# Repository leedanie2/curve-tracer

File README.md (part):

# Curve Tracer

A low-cost semiconductor curve tracer for small-signal MOSFETs and diodes. It
sweeps the voltage across a device, measures the current through it with
four-wire (Kelvin) sensing, and streams the result over USB. A Python host then
fits the device's parameters (threshold voltage, transconductance, channel-length
modulation; diode ideality, saturation current and series resistance) and writes
them out as a SPICE `.model` card. The aim is to close the loop
`device → measurement → model → simulation` on hardware I designed.

It is built as an assembled PCB carrying an STM32 Nucleo-F303RE, with firmware
in C and a Python host.

## Status, 2026-11-13

Every claim below is one of five things. **Measured** means on the bench,
from the board. **Analysis** means arithmetic on measured figures, or a
comparison with published ones. **Simulated only** means LTspice, ngspice
or the firmware simulator, with no bench result yet. **Done** covers work that needs no
measurement. **Not done** is what's left. Nothing in this README goes past
its row.

| Claim | Status | Evidence |
|---|---|---|
| Analog design: stability into capacitive loads, current limiter, sense-amp CMRR | Simulated only | LTspice sims 02–11, [below](#simulation-results) |
| Schematic and 2-layer PCB, DRC/ERC clean, topology checker | Done | `hardware/review/pass2/` |
| Five boards fabricated and fully assembled by JLCPCB | Done | `hardware/ORDER.md` |
| Firmware runs on the Nucleo; host link works | Measured | 2026-10-30 to 2026-11-13 captures (`host/h4/`) |
| Board powers up; loop quiet into 200 Ω ‖ 100 nF (L1), idle and 0.1–6 V | Measured | 2026-11-03 and 2026-11-08, [bench record](#bench-record) |
| 100 nF alone across a two-terminal device keeps the loop quiet, on a breadboard fixture | Measured, 2026-11-13: idle, 0.2–6 V, beside 0.1% resistors and through a diode sweep. Sim 16 predicted it. MOSFET families stay on L1 | [Session 3](#session-3-board-2-2026-11-13) |
| Loop stable with nothing connected (C1 empty) | **Measured: fails.** Oscillates at 0.8–1.15 MHz | [The open-load oscillation](#a-measured-finding-the-open-load-oscillation) |
| Root cause of the oscillation | Analysis and simulation | Sims 12–14 |
| C1 in the 2.2–4.7 pF range damps it | Simulated only (TI's op-amp model, open load and 200 Ω ‖ 100 nF) | Sims 14–14f; not fitted, since 0603 can't be hand-fitted here. Rev 2 specifies 4.7 pF |
| 470 Ω across the device keeps the loop quiet | **Measured: fails.** Oscillates at 781 kHz with nothing running. Sim 13 had predicted quiet | [Working around it](#working-around-it-until-rev-2) |
| L1 (200 Ω ‖ 100 nF) across the device keeps it quiet, and why | Measured; the mechanism is analysis and simulation (sim 15) | [Working around it](#working-around-it-until-rev-2) |
| Voltage accuracy against a DMM | Measured, 3 points: within the DMM's own ±0.8%. Blueprint §7's < 0.5% needs a better reference | [Accuracy](#accuracy-against-a-dmm) |
| Current against voltage, 0.1% resistors | **Measured**, 2026-11-13: current reads 0.1–0.8% high against the voltage, or up to 1.5% if the resistors sat behind the fixture's ~0.5 Ω (analysis; MVP card §F decides). Zero −0.09 to −0.14 mA. Absolute current ±1.6% (±2.3%) uncorrected, set by the voltage's DMM check | [Session 3](#session-3-board-2-2026-11-13) |
| The current channel with nothing drawing current | **Measured**: it reads a floor, 0.198 + 0.104 · V mA, not its zero; the difference amp's swing limit (analysis, TI's datasheet). The host leaves such rows out | [Session 3](#session-3-board-2-2026-11-13) |
| R_p subtraction, channel model, extraction, `.model` card, ngspice overlay | Done; run on bench data 2026-11-08 and 2026-11-13 | `host/`, 203 tests |
| Diode parameters from a real diode | **Measured**: 1N4148, n 1.789, I_S 2.68 nA, R_s 1.14 Ω. Systematic from the zero and the channel model: n 1.788–1.831, I_S 2.15–3.69 nA, R_s 1.01–1.14 Ω | [Headline figure](#headline-one-real-diode-measured-and-simulated) |
| Measured vs simulated overlay, real diode | **Measured**, against ngspice running the extracted card: 0.51 mV rms over 0.2–20 mA | [Headline figure](#headline-one-real-diode-measured-and-simulated) |
| Diode against published 1N4148 models | Analysis: between LTspice's and Nexperia's, 8–24 mV from each | [Session 2](#session-2-board-2-2026-11-08) |
| MOSFET `.model` card from a real part | **Fixture-dependent, under investigation.** Measured 2026-11-13 (2N7000, Level 1, 16 gate steps, saturation only), but on a fixture that put ~0.4 Ω in its source path (analysis), and 86 mV of gate from the same part on 11-08 is unexplained. Not a headline result | [The 2N7000 card](#the-2n7000-card-fixture-dependent-under-investigation) |
| MOSFET threshold | **Measured**, 2026-11-08: **V_GS(th) 2.147 V at 1 mA**, model-free; the measured threshold. The same part on 11-13 needed ~90 mV more gate, under investigation | [Session 2](#session-2-board-2-2026-11-08) |
| Waves on the scope with a MOSFET in place | Measured on the scope: 748 kHz in an 11-08 hold; none in an 11-13 hold; waves during both sweeps. Under 10 µA in the DC readings. Sustained or not: open | [Session 3](#session-3-board-2-2026-11-13) |
| Blueprint §6 closed loop: build a circuit with the extracted model, compare | Not done | |
| Short-circuit and thermal test (H4 Block 4) | Not done | No heatsink insulator at the bench |
| Current ranges 2 and 3 (fitted on the board) | Not done | Out of scope |

### Headline: one real diode, measured and simulated

*Measured, 2026-11-08, board 2: a 1N4148 swept to 20 mA, four-wire,
`device → measurement → model → simulation` closed on real data. The dots
are the measurement, with L1's current and the instrument's zero subtracted
(`host/h4/mvp_17_diode_rp.csv`). The line is ngspice-47 running the
`.model` card the host fitted from those dots
(`host/h4/mvp_17_diode.lib`: n 1.789 ± 0.003, I_S 2.68 ± 0.06 nA,
R_s 1.135 ± 0.016 Ω, statistical). **The larger uncertainty is
systematic.** The instrument's current zero measured −0.087 mA on the
calibration and −0.099 mA on the diode's own off rows. Refitted at each,
the values span n 1.788–1.831, I_S 2.66–3.69 nA, R_s 1.01–1.14 Ω. The
0.1% resistor holds of 2026-11-13 add two smaller terms. Current reads
0.1–0.8% high against voltage, and the voltage channel may read 10 mV low.
That would take I_S to 2.15 nA, so in all **n 1.788–1.831, I_S
2.15–3.69 nA, R_s 1.01–1.14 Ω**. n and I_S trade off against each other,
so the curve itself moves at most 3 mV, or 10 mV with the voltage
offset. Residual 0.51 mV rms over the 60 points above 0.2 mA. Of that, −0.38 mV is a constant: ngspice's default 27 °C against
the fit's 300 K. Hollow points sit below 5 current LSB and are not fitted.
The curve lies between the two published 1N4148 models compared, 8–24 mV
above LTspice's and 10–14 mV below Nexperia's (diode temperature not
measured; ~2 mV/°C).*

*Why this capture stays the headline after a second one (2026-11-13).*
On 11-08 L1 lifted every reading clear of the current channel's floor, and
its own calibration line gave the zero at the same voltages. The 11-13
capture, on 100 nF alone, has 39 of 100 rows on the floor, so its zero has
to be borrowed from holds at other voltages. Its n also moves 2.5× more
with the low-current cut. That rule was set before comparing values
([session 3](#session-3-board-2-2026-11-13)). The 11-13 diode reads 23–44 mV
higher at equal current, and it is the same diode. A fixture resistance
of ~0.5 Ω between the Kelvin points and the part accounts for its higher
R_s, and for 0.6 mV of the 22 mV at 1 mA. The rest is unexplained
(analysis; MVP card §F tests it).

*KiCad render of the routed board (Pass 2, 2026-10-06), not a photograph. The
Nucleo plugs into the two sockets on the right. Board size 135 × 92 mm, two
layers.*

## What it can measure

The design envelope. Nothing in it is measured yet unless the row says so.

| | |
|---|---|
| **Devices** | Two-terminal devices (diodes, LEDs, resistors) and **N-channel enhancement MOSFETs**. **No BJTs**: the step source is a voltage through 1 kΩ, not a base current. **No P-channel or depletion parts**: the gate source is 0 to +10 V |
| **Polarity** | **One quadrant.** Drain/anode at 0 to +10 V and current into the device only. No reverse bias |
| **Voltage** | 0–10 V by design; 9.06–9.73 V is the ceiling at 50 mA (analysis: the PTC fuse's drop). **Floor measured: 0.18 V** at the node (DAC code 0, 2026-11-08), well below the 0.66 V the DAC's guaranteed 0.2 V minimum implies. Above ~6.6 V the Nucleo's LED loads the DAC: estimated, not measured |
| **Current** | 0–50 mA on range 1, 40.3 µA per ADC count, averaged 64× per point. Hardware limiter ~75 mA (simulated); firmware limit set per device. **Floor measured:** with nothing lifting it, the channel reads no lower than 0.198 + 0.104 · V mA, so on 100 nF alone a device registers only above ~0.4–0.5 mA at 0.6 V; on L1, from 0.2 mA |
| **Mode** | **DC only.** No pulsed mode, so the device heats at its own dissipation |
| **Accuracy** | Voltage: within a 3½-digit DMM's ±0.8% (2026-11-08). Current against voltage: 0.1–0.8% high, from 0.1% resistors (2026-11-13), or up to 1.5% if they sat behind the fixture's ~0.5 Ω. So absolute current is ±1.6% (±2.3%) uncorrected. Zero −0.09 to −0.14 mA, subtracted. [DMM](#accuracy-against-a-dmm), [resistors](#session-3-board-2-2026-11-13) |
| **Until rev 2** | The loop needs ≥ 100 nF across the device. **Two-terminal parts:** 100 nF alone, on a breadboard fixture (measured quiet, 2026-11-13), with nothing to subtract. **MOSFET families, and a diode's bottom decade:** L1, 200 Ω ‖ 100 nF. The host subtracts L1's current from a calibration sweep (~1.5 µA at 0.75 V on 2026-11-08), and L1 lifts the channel off its floor. A plain 470 Ω was not enough (measured) |

**What it's for.** It replaces the undergraduate I-V lab done by hand with
a bench supply and two meters, one point at a time, for small diodes, LEDs
and small N-MOSFETs. It records the curve with four-wire sensing and fits a
SPICE model from it. **What it isn't:** a general-purpose commercial curve
tracer or source-measure unit. Those cover high voltage and current, both
polarities, pulsed measurement, BJTs and picoamp leakage. This covers none of
them.

## Limitations

What the results above do not cover, as of 2026-11-13:

- **Waves on the scope with a MOSFET in place are unexplained.** On 11-08
  a hold's counter locked at 748.5 kHz; on 11-13 a hold showed nothing
  periodic, but waves showed during both family sweeps. They move the DC
  readings by under 10 µA. Whether they are sustained, and which loop they
  come from, is open.
- **The gate voltage is commanded, not read back.** The read-back step
  (H4 P1b) was skipped, so every V_GS, including the 2N7000's threshold,
  carries the gate DAC's unmeasured gain error.
- **The MOSFET card is narrow and fixture-dependent.** It is Level 1,
  fitted over V_GS 2.45–2.75 V, and holds in saturation only: below
  V_DS ≈ 0.4 V it reads up to 4.2 mA low, because the part is in moderate
  inversion. It was taken on a fixture that degenerated the source by
  ~0.4 Ω (analysis). It stays under investigation until MVP card §F reruns
  it with the Kelvin pair and the force wires at the part.
- **The same two parts read differently from one session to the next.** On
  11-13 the 1N4148 read 23–44 mV higher, and the 2N7000 needed ~90 mV more
  gate, than on 11-08. *Analysis:* ~0.4–0.6 Ω of breadboard links
  between the Kelvin points and the parts explains the resistive part of
  both, and of L1's fitted R. It can't explain a constant +21 mV on the
  diode or +86 mV of gate. Self-heating during the sweeps can't either: it
  is under 0.3 K per sweep, and the 2N7000's is the wrong sign. That leaves
  the parts' surroundings, which weren't measured. The constants are
  unexplained.
- **Blueprint §6's closed loop is not done.** The diode's model is checked
  against its own measurement. No circuit has been built around it and
  compared with the bench.
- **Absolute accuracy rests on a 3½-digit DMM.** The 0.1% resistors fix
  current against voltage to 0.1–0.8% (1.5% if the fixture's resistance
  sat in series with them), but voltage itself is bounded only at the DMM's
  ±0.8%. Part of the spread is one open question: a −10 mV voltage offset,
  or a curved common-mode term. Section F's holds decide both.
- **The bench supply can be off without the instrument knowing.** Nothing
  reads +15 V. On 11-13 three runs were taken with it off and produced
  plausible numbers; the card now checks the supply's display after every
  part swap.

## A measured finding: the open-load oscillation

**Measured, 2026-11-03, board 2, C1 empty.** Holding 6 V into
200 Ω ‖ 100 nF, the loop was quiet. With nothing connected it oscillated
intermittently at **0.79–1.15 MHz**, from over 0.2 V to over 2 V
peak-to-peak (the scope clipped). In the run with the largest
oscillation, the current read 2.2 mA high. (The other two runs' 0.83 mA,
first read as error too, is the channel's floor with nothing drawing
current, measured on 2026-11-13 with the loop quiet.) Full data is in
[Block 1](#block-1-measurements-first-power-up-board-2) below and in
[`docs/characterization.md`](docs/characterization.md).

**Root cause (analysis, checked in LTspice sims 12–14).** With no load, the
pass transistor (Q1) carries only ~0.2 mA. Its emitter resistance is then
~130 Ω, and it drives the ~1 nF of the protection diode D3 through ~41 Ω.
That puts a pole near 0.8 MHz inside the loop. Under the 200 Ω load, Q1 runs
at 26 mA and the pole moves far out. So the problem depends on the load,
which is why it shows up well below the ~3 MHz the design had estimated for
the op-amp's input-capacitance pole. The generic op-amp model reproduces
the oscillation only with 20–30 pF of input capacitance added. TI's own
OPA2197 model needs none: at open load it rings at 0.91 MHz, each
half-cycle 0.83× the last, close to sustained.

**The fix (simulation, sims 14–14f, TI's model).** The board has an empty
footprint for C1, a capacitor across the feedback resistor. The predicted
value is **3.4–3.9 pF**. At 6 V open load, 3.3 pF cuts the ring to 0.40×
per half-cycle, and 4.7 pF removes it, with no sign of over-compensation.
The generic model's figure, 8.6–12.9 pF, would over-compensate. Because the
bench was less damped than TI's model, rev 2 specifies **4.7 pF**
(`hardware/DECISIONS.md` R2-4). That rests on one vendor model. C1 is a
0603 part, which I can't fit reliably by hand, so it isn't fitted on rev 1.
Rev 2 has the assembler fit it.

### Working around it until rev 2

**Measured, 2026-11-08.** Sim 13 predicted that 470 Ω clamped across the
device would keep the bare loop quiet. On the bench it didn't: with nothing
running, 470 Ω oscillated at **781 kHz**, over 205 mV peak-to-peak. The
loop is never fully off. The sweep DAC can't reach 0 V, so at idle it holds
the node at 0.18 V, and that is where 470 Ω failed. L1, the
200 Ω ‖ 100 nF load from Block 1, was quiet at idle and at every level
tried, 0.1–6 V. So every device now shares J6 with L1, and the host
subtracts L1's current, calibrated by a sweep of L1 alone.

**Why it is the 100 nF (analysis, checked in sim 15 with TI's model).**
The load puts a lag of 20–30° into the loop. Without the 100 nF that lag
sits at 1.5–5 MHz, around crossover, on top of the op-amp's own excess
phase. With it, the same lag moves two decades down, to 20–60 kHz, where
the loop has phase to spare. L1 also biases Q1 harder (0.9 against
0.4 mA). In sim 15 that only shrinks a ring the 100 nF removes outright.
Sim 13's error was its model. The generic op-amp with 20–30 pF added had
been fitted to reproduce one bench point, the open-load oscillation, and
it was optimistic everywhere else. TI's model is optimistic too, though
less so: it rings and decays where the bench sustained. Phase 0 had the
same lesson about the BD139 model (design decision 2 below).

**100 nF alone, on a breadboard fixture (measured, 2026-11-13).** Sim 16
said the capacitor, not the resistor, was doing the work, and the bench
agreed. With only 100 nF across D–S, plugged into a breadboard with the
Kelvin pair at the device's own columns, the loop showed no periodic wave
at idle, at 0.2, 1 and 6 V, beside 0.1% resistors, or through a diode
sweep. Two-terminal parts no longer need L1, so there is no current to
subtract. MOSFET families still do: with no resistor, the node can't
discharge between gate steps below ~0.6 V. One practical lesson: the
breadboard's centre channel splits each column. The first MOSFET attempt
had its legs across it, its gate was undriven, and the family came out
flat.

## Design decisions

Each of these is backed by a simulation, a calculation or a datasheet figure.
The full record, part by part, is [`hardware/DECISIONS.md`](hardware/DECISIONS.md);
the reasoning is in [`curve_tracer_blueprint.md`](curve_tracer_blueprint.md).

1. **Isolate the capacitive load; don't compensate it.** The obvious fix, a
   capacitor across the feedback resistor, made the loop *worse* at every value
   from 1 to 100 pF. Instead, a 22 Ω `R_iso` sits outside the loop, and Kelvin
   sensing makes its 1.1 V drop at 50 mA harmless (sims 02, 03).
2. **Model fidelity decided the answer.** With a generic 2N2222 model the
   loop looked unconditionally stable. ST's published BD139 model (f_T ≈ 54 MHz,
   C_jc 36 pF) oscillated immediately. A third-party BD139 model found online
   had placeholder junction capacitances (`CJE = CJC = 1e-11`) and would have
   hidden the problem. A separate false result, 9% overshoot, turned out to be
   a solver timestep artefact. Capping the timestep removed it
   (blueprint §12).
3. **Base resistor 330 Ω, not 680 Ω.** Both are stable in simulation, but
   680 Ω leaves ~44° of implied phase margin, against ~59° for 330 Ω. The
   op-amp's own input capacitance adds a pole the simulation does not contain
   (estimated 5–9 pF), and from 44° that loss is not recoverable (sim 08).
4. **A base-emitter clamp diode.** On a falling edge the op-amp slams to its
   rail while the load holds the emitter up, and V_BE reaches −9 V against the
   BD139's 5 V rating. A 1N4148 holds it to −0.74 V (sims 08, 09).
5. **A hardware current limiter**, Q2 across a 10 Ω `R_sense`, independent of
   the firmware limit. 15 Ω was rejected because its trip point (~49–50 mA)
   falls inside the sweep range (sims 10, 11).
6. **Buffer the difference amplifier's inputs.** Unbuffered, the resistor
   bridge alone draws 475.6 µA through the shunt with nothing connected. That
   is 0.95% of full scale on range 1 and makes range 3 unusable. The design
   went from two to three dual op-amps (sims 06, 07).
7. **0.1% resistors in the difference amp**, because common-mode rejection
   comes from resistor matching alone and cannot be trimmed afterwards (sims 04,
   05).
8. **One board revision, designed for it.** There is a test point on every
   node, footprints for alternate values, headers instead of soldered
   connections, and a footprint for the compensation capacitor, left empty.
   JLCPCB assembled every part on all five boards.
9. **The host slices on *measured* voltage, never the commanded voltage.** At
   one commanded voltage, curves at different currents reach different real
   voltages because of `R_iso`'s drop. Grouping by the command gives a
   convincing but wrong threshold voltage. The diode fit solves n, I_S and R_s
   jointly; a windowed semilog fit was 13% wrong on n at R² = 0.9965
   ([`host/README.md`](host/README.md)).

Two decisions changed when they met reality. They are recorded as rev-2 items,
not hidden:

- **The F303RE has no DAC2.** The board routed the sweep to a pin with no DAC.
  This was found at the first real firmware build. The fix is a jumper on the
  Nucleo from PA5 (DAC1_OUT2) to PA6. PA5 also drives the Nucleo's LED, which
  loads the DAC and may cut sweeps above about 6.6 V (estimated, not yet
  measured; `DECISIONS.md` R2-3).
- **The empty compensation-capacitor footprint assumed hand-fitting**, a
  0603 part, which I could not do reliably. Rev 2 has JLCPCB fit it, at
  4.7 pF (`DECISIONS.md` R2-2, R2-4).

## Simulation results

**All of these are simulated.** LTspice files are in [`sim/`](sim/), with
per-file detail in [`sim/README.md`](sim/README.md). The sweep-source sims
ran at R_f = 23.3 kΩ; the board has 23.2 kΩ, a 0.4% difference below the
precision of every figure here.

| Question | Result (simulated) | Simulation |
|---|---|---|
| Capacitive load the sweep source tolerates | Without `R_iso`: stable to ~1 nF, oscillating by 2.2 nF. With 22 Ω: clean from 100 pF to 100 nF | LTspice, `sim/03_sweep_source_load_sweep.asc` |
| Small-signal step, 100 nF ‖ 200 Ω, R_B = 330 Ω | 10.34% overshoot, 0.50 µs to 1%, ζ ≈ 0.59 (~59° implied phase margin) | LTspice, `sim/08_sweep_source_rb_sweep.asc` |
| Reverse V_BE on a falling edge, 100 nF load | −7.72 V → −0.73 V (200 Ω load); −8.98 V → −0.74 V (open), with the clamp | LTspice, `sim/08…`, `sim/09_sweep_source_clamped.asc` |
| Current-limiter trip; hard short | 75.2 mA through R_sense; 107.0 mA load; BD139 at 891 mW | LTspice, `sim/11_limit_sizing.asc` |
| Overshoot on recovery from a short, 100 pF load | 14.8 V peak (+48%); back within 1% in 1.9 µs | LTspice, `sim/10_current_limit.asc` |
| Difference-amp CMRR, worst-case 0.1% corner | 74.42 dB | LTspice, `sim/04_diffamp_cmrr.cir` |
| CMRR, 500-run Monte Carlo at 0.1% | median 88.26 dB, p5 79.43 dB, min 76.20 dB | LTspice, `sim/05_diffamp_mc.cir` |
| Phantom current, unbuffered diff amp, no DUT | 475.6 µA at 1 Ω shunt | LTspice, `sim/06_diffamp_loading.cir` |

*Simulated: CMRR over 500 Monte Carlo runs with 0.1% resistors
(`sim/05_diffamp_mc.cir`). LTspice draws uniform, independent tolerances, so
this spread is conservative.*

Sims 02–11 didn't model D3's ~1 nF, the PTC or the Kelvin divider; sim 12
added them. That is the gap the board fell into at open load: see
[the finding](#a-measured-finding-the-open-load-oscillation).

### Host software, closed loop on a simulated device

`ct_sim` is the real firmware core (sweep engine, CSV writer, command parser,
current limit), compiled for the desktop with a modelled device behind it. The
host's tests feed it known parameters, run a sweep, extract the parameters, and
require the same values back. **Simulated, `ct_sim`:**

| Fed in | Recovered |
|---|---|
| V_th = 2.15 V | 2.1502 V (0.2 mV) |
| k = 0.055 A/V² | 0.05506 (0.1%) |
| λ = 0.012 /V | 0.01192 (0.7%) |
| diode n = 1.75 | 1.7605 (0.6%) |
| diode I_S = 2.5 nA | 2.73 nA (9%; quantisation, explained in [`host/README.md`](host/README.md)) |
| diode R_s = 0.6 Ω | 0.5914 Ω (1.4%) |

With a 470 Ω resistor beside the device, its current subtracted, and the
extracted card run back through ngspice, the simulated diode comes back as
n = 1.751, I_S = 2.52 nA and R_s = 0.601 Ω, with a 0.63 mV rms residual
([`host/README.md`](host/README.md#from-a-capture-to-the-overlay)). 203
host tests and the firmware unit suites pass. That validates the software
path only. It says nothing about the analog hardware.

## Block diagram

```
   Nucleo-F303RE                     Board
  ┌──────────────┐
  │ DAC1_OUT2 PA5├─shunt─► PA6 ─► [×3.32] ─► [OPA2197 + BD139 follower] ─► R_sense ─┬─► R_iso 22Ω ─► PTC ─► shunt ─► DUT drain
  │              │                                ▲      │                         │                        │            │
  │              │                                │   [Q2 current limiter]        │                   [buffered     [Kelvin pair
  │              │                                └─────────── feedback ──────────┘                   diff amp ×20]  ÷4 + buffer]
  │ ADC1  PA0   ◄├──────────────────────────────────────────────────────────────────────────────────────────┘            │
  │ ADC2  PC0   ◄├───────────────────────────────────────────────────────────────────────────────────────────────────────┘
  │ DAC1_OUT1 PA4├─────► [×3.32] ─► [buffer] ─► 1 kΩ ─► DUT gate  (12 V Zener clamp)
  │ USART2 ◄─────┼─► ST-LINK VCP ─► USB ─► Python host
  └──────────────┘                                                     DUT source ─► GND        (SMAJ12A TVS on the drain)
```

Per point: set the gate DAC, set the drain DAC, wait to settle, oversample both
ADCs 64×, send a CSV row. The host recomputes current and voltage from the raw
accumulators and checks them against the firmware's own numbers.

## PCB

*KiCad render, top view (`hardware/review/pass2/`). The analog section is on the
left, with the Nucleo sockets J7/J8 on the right. Q1's heatsink keep-out is
marked at the top left.*

- The analog-critical nets were routed by hand: the feedback node, the
  inverting input, the base drive, the shunt and Kelvin pairs. The rest was
  autorouted (Freerouting) with those nets locked
  ([`hardware/README.md`](hardware/README.md), *Routing policy*).
- DRC and ERC are clean with schematic parity
  (`hardware/review/pass2/metrics.txt`). `check_topology.py` asserts the
  circuit's topology from the netlist (59 checks) and catches all 14 faults
  its self-test plants, which ERC passes.
- Every net that crosses the ground split, and its distance to the star
  tie: [`p2_split_crossings.png`](hardware/review/pass2/p2_split_crossings.png).

## A bench finding: the ST-LINK serial link on macOS

The first time the host talked to the Nucleo (2026-10-30), every command timed
out. A single host write of **16 bytes or more** stopped the ST-LINK/V2-1's
virtual COM port passing data from host to target until the USB cable was
replugged. This was on firmware V2J33M25, under macOS. Writes of 8 bytes,
5 ms apart, got through. The first write after the ST-LINK enumerates was also
lost.

To rule out the firmware, I read the MCU state over SWD while the link was
wedged. The main loop was idle, USART2 was configured, and no bytes were
reaching the RX pin (PA3). The fault is upstream of the MCU, in the ST-LINK's
USB-to-UART bridge. The fix is host-side: the transport writes in 8-byte
chunks 5 ms apart and opens with a blank line, which the firmware's parser
ignores. A regression test checks that no single write reaches 16 bytes. After
the fix, two hold runs back to back worked after a replug (commit `2debc57`).
An ST-LINK firmware upgrade might also fix it. That is untested.

## Bench record

### Block 1 measurements: first power-up, board 2

**Measured, 2026-11-03**, from [`hardware/MVP_CARD.md`](hardware/MVP_CARD.md)
(raw data in `host/h4/mvp_*.csv`; full log in
[`docs/characterization.md`](docs/characterization.md)). A pass here shows
no sustained oscillation under a DC hold. It does not measure phase margin
or ringing (H4 step 5, not run). C1, the compensation capacitor, is empty.

| Measurement | Pass band | Result |
|---|---|---|
| Supply current at power-up | 3–25 mA | 3 mA, supply in CV (rails not checked) |
| Scope baseline at TP3, idle (B) | < 10 mV p-p | 12.0 mV, board powered |
| Hold 6 V into 95.2 nF ‖ 202 Ω (measured): p-p at TP3 | ≤ B + 5 mV | 12–30 mV; 26.8 mV, and 26.0 mV with the probe ground moved. Broadband, no periodic component |
| … measured V, I | 4.8–5.5 V, 23–29 mA | 5.193 V, 25.74 mA (5.193 V / 202 Ω = 25.71 mA) |
| Hold 6 V, open load: p-p at TP3 | ≤ B + 5 mV | **Oscillates**: > 0.2 V to > 2 V p-p (clipped), varying run to run |
| … measured V, I | 5.7–6.2 V, ≤ 0.5 mA | 6.006–6.192 V; 0.830 and 0.832 mA in two runs, 2.998 mA in the run with the largest oscillation. *Corrected 2026-11-13:* the 0.83 mA is the channel's floor with nothing drawing current (0.82 mA at 6 V with the loop quiet), so the 0.5 mA band could not pass. Only the 3.0 mA was oscillation error |
| Oscillation frequency | — | ~0.79 MHz (read while clipped) and 1.149 MHz |
| **Block 1 verdict** | | **Fail**: no sustained oscillation with a 200 Ω ‖ 100 nF load; intermittent ~0.8–1.15 MHz oscillation at open load, C1 empty |

The 26 mV under load is over the card's limit, but it is broadband noise,
not oscillation. The limit allowed less than 2 DAC steps at TP3.

### Session 2, board 2, 2026-11-08

**Measured**, from [`hardware/MVP_CARD.md`](hardware/MVP_CARD.md) §D
(raw data in `host/h4/mvp_13c*` to `mvp_18*`; full log, with the analysis
labelled, in [`docs/characterization.md`](docs/characterization.md)). C1
empty, L1 across D–S throughout.

| Step | Result |
|---|---|
| 470 Ω across D–S, idle | **Oscillates**, 781 kHz, > 205 mV p-p. Session switched to L1 |
| L1, idle / 0.1 V / 0.3 V | Quiet: 22.4 / 20.0 / 20.4 mV p-p, noise only |
| Sweep floor | 0.18–0.19 V at the device (DAC code 0) |
| L1 calibration sweep | R = 201.31 ± 0.06 Ω, zero −0.087 mA, max residual 0.016 mA |
| Accuracy, 3 points | See below |
| 1N4148 ‖ L1 | n 1.789, I_S 2.68 nA, R_s 1.14 Ω; zero systematic n 1.788–1.831, I_S 2.66–3.69 nA, R_s 1.01–1.14 Ω. The [headline figure](#headline-one-real-diode-measured-and-simulated) |
| 2N7000 ‖ L1, 14 gate steps 1.5–2.8 V | V_GS(th) 2.147 V; family below. Stopped at the 40 mA limit on 2.8 V, so 2.9 and 3.0 V didn't run |

**The instrument's current zero.** With L1's current removed, an off
device read −0.09 mA in every capture: the calibration, the diode below
0.25 V, and the MOSFET's off steps. The host used to subtract L1's
`V / R` but leave that zero in. At the diode fit's 0.2 mA floor the zero is
43% of the current, and leaving it in read n as 1.651 and I_S as 0.83 nA.
The host now subtracts the calibration's whole line, zero included. That
fits 2.7× tighter, with 2.4× less residual.

#### Accuracy against a DMM

L1 held at three levels, DMM (BK 2704A, 3½ digits) across J6. The current
reference is V_DMM / R_DMM, with R_DMM = 200 Ω.

| Hold | Instrument V | DMM V | ΔV | Instrument I | V_DMM / 200 Ω | ΔI |
|---|---|---|---|---|---|---|
| 2 V | 1.7337 V | 1.74 V | −6.3 mV | 8.526 mA | 8.700 mA | −0.174 mA |
| 4 V | 3.4631 V | 3.47 V | −6.9 mV | 17.149 mA | 17.350 mA | −0.202 mA |
| 6 V | 5.1930 V | 5.20 V | −7.0 mV | 25.779 mA | 26.000 mA | −0.221 mA |

- **Voltage:** gain −0.02%, offset −6 mV against the DMM. The DMM is good
  to ±0.8% + 10 mV, so the error is bounded at that, not measured below it.
- **Current:** gain −0.28%, offset −0.15 mA against V_DMM / R_DMM. That
  reference is good only to about ±3%, because R_DMM is read on the 2 kΩ
  range (±6 Ω), and all three errors sit inside it. The offset agrees
  with the instrument's own zero, −0.087 mA, to about one DMM count.
- **ADC reference:** 3.30 V at TP8, ±1.1% on the DMM.
- Blueprint §7 asks for <0.5% voltage and <1% current error. Showing that
  needs a 5½-digit meter and 0.1% resistors; this session can't.

#### The 2N7000

*Measured, 2026-11-08, board 2: a 2N7000 with L1's current and the
instrument's zero subtracted (`host/h4/mvp_18_mosfet_rp.csv`). Fourteen
gate steps, commanded, not measured. The sweep stopped where the total
current passed 40 mA (×), so 2.9 and 3.0 V were never applied.*

| | Value | Note |
|---|---|---|
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
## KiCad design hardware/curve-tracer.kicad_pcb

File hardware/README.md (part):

# hardware/ — PCB revision

KiCad project for the curve tracer PCB. Scope, dates and the non-negotiable
layout constraints live in `curve_tracer_blueprint.md` **§14**; the build
phases and date gates are **§9**. This file is the toolchain and the routing
policy.

MVP scope, unchanged from `firmware/README.md`: **range 1 only, DC sweep, no
pulsed mode, no auto-ranging.** **One revision only** — §14.4 lists what that
buys (test points everywhere, alternate-value footprints, headers over solder).

```
hardware/
├── README.md       ← this file
├── DECISIONS.md    ← where every value on the board came from: blueprint, sim or bench
├── H4_CARD.md      ← printable bring-up card: numbered steps, settings, pass/fail, blanks to fill
├── CONTINGENCY.md  ← if the board oscillates at bring-up: Part A goto steps, Part B the reasoning
├── ORDER.md        ← everything to buy, by vendor (JLCPCB, LCSC, DigiKey), with stock, prices and what to verify
├── curve-tracer.kicad_pro
├── curve-tracer.kicad_sch   ← H1, captured Oct 5, 2026
├── curve-tracer.kicad_pcb   ← H2, routed Oct 6, 2026: 135 × 92 mm, two layers
├── fp-lib-table    ← registers lib/ as footprint library `curve-tracer`
├── lib/curve-tracer.pretty/  ← two project footprints: J3/J4 range select, J7/J8 Nucleo socket
├── tools/check_topology.py   ← asserts the §3 / §14.5 topology; run after every edit
├── tools/export_fab.py       ← writes everything in fab/; run before every order
├── fab/            ← engineering BOM, Gerbers + drill, and the JLCPCB upload set in fab/jlc/
├── review/         ← layout renders and metrics, pass1/ and pass2/: the evidence for the write-up
├── analysis/       ← gitignored; kicad-happy analyzer runs
└── datasheets/     ← gitignored; re-sync with the lcsc skill's sync_datasheets_lcsc.py
```

Symbols are stock KiCad 10. So are the footprints, except two. J3/J4 is a
stock 2×3 header with silkscreen added (RNG1–RNG3 per row, and "J3=J4
POS"). J7/J8 is the stock 2×19 socket with its pad numbering mirrored for a
board the Nucleo plugs into (`DECISIONS.md` L-2). Each symbol carries `MPN`, `Manufacturer`, `LCSC` and
`Provenance` fields. `Provenance` links to the symbol's row in `DECISIONS.md`.

### Checking the schematic after an edit

The schematic is the source of truth and is edited by hand from here on. ERC
proves it is legal; it does not prove it is the circuit §3 describes. Run
both:

```
kicad-cli sch erc --severity-all hardware/curve-tracer.kicad_sch
python3 hardware/tools/check_topology.py --self-test
```

`check_topology.py` exports the netlist through kicad-cli and asserts every
connection §3 depends on: each op-amp pin, the three gains and the ÷4, the
§14.5(5) tap position, limiter and clamp polarity (D3 included), the Nucleo
pin map, star ground, and test-point coverage. It also fixes the list of
parts on the DUT node (blueprint §3.3), so a part added there fails until its
current has been checked against range 3. `--self-test` also plants sixteen faults that
ERC passes, and fails if any goes uncaught. Change a value on purpose →
change the matching assertion in the same commit.

**For H2:** KiCad ships a `STM32_Nucleo-64_Morpho` project template
(`KiCad.app/Contents/SharedSupport/template/`). Its board places the two
2×19 morpho sockets at the correct spacing, with the mounting holes. Take
the CN7/CN10 geometry from it rather than measuring a Nucleo.

---

## Toolchain

| | |
|---|---|
| **EDA** | **KiCad 10.0.6** (schematic capture, layout, gerber/BOM/CPL export) |
| **Review** | **`kicad-happy` v2.3.0** agent skills — ERC/DRC review, netlist and footprint checks, BOM and CPL sanity before the order goes out |
| **Assembly** | **PCBA** — assembled by the fab, **express shipping** (§14.3, §14.3a) |
| **Routing** | Analog-critical nets **by hand**. Everything else autorouted with **Freerouting v2.5.0** (`DECISIONS.md` P-6) |

### Installed state

All five are installed on this machine: the first four as of **Oct 5, 2026**,
Freerouting on Oct 6. `kicad-happy` must be present before **H1** (§9), and
it is.

| | |
|---|---|
| KiCad | **10.0.6**, `/Applications/KiCad/KiCad.app`, CLI at `/Applications/KiCad/KiCad.app/Contents/MacOS/kicad-cli`. Installed from the official universal `.dmg`, **not** Homebrew — the cask writes to a root-owned path and wants a sudo password. Upgrades are therefore manual: fetch a new `.dmg` from kicad.org |
| `kicad-happy` | **v2.3.0** (`aklofas/kicad-happy`), cloned to `~/.claude/kicad-happy`, with all **11** skills symlinked into `~/.claude/skills/` — `kicad`, `spice`, `emc`, `datasheets`, `bom`, `digikey`, `mouser`, `lcsc`, `element14`, `jlcpcb`, `pcbway`. Global, so available in every project. **Upgrade with `git pull` in that clone** — upstream documents `/plugin update` as unreliable, which is why this is a symlink install rather than a marketplace plugin |
| KiCad library tables | Default global `sym-lib-table` / `fp-lib-table` copied from the bundled template into `~/Library/Preferences/kicad/10.0/` on Oct 5, 2026. KiCad's first-run dialog normally does this; it had never been run here, so `kicad-cli sch erc` reported every symbol as an unknown library |
| Freerouting | **v2.5.0**, `~/.local/share/freerouting/freerouting-2.5.0.jar`, from the GitHub release (`freerouting/freerouting`). Installed Oct 6, 2026; SHA-256 `f6f51bb0…ffeb5de3c7` matches the release's published digest. Runs on Homebrew `openjdk` 25.0.2, which was already installed. **Headless only**: `java -Djava.awt.headless=true -jar <jar> --gui.enabled=false -de board.dsn -dr board.rules -do board.ses`. Even `--version` hangs once the GUI starts. Not a KiCad plugin: the board goes out as a SPECCTRA `.dsn` and comes back as a `.ses` (P-6 has the method). Upgrade by downloading the new release JAR and checking its digest |
| `ngspice` | **47**, Homebrew (`/opt/homebrew/bin/ngspice`), installed Oct 5, 2026 for the `spice` skill's subcircuit checks. LTspice stays the tool for `sim/`; the skill cannot drive the CrossOver bottle. Upgrade with `brew upgrade ngspice` |

`kicad-happy` needs Python 3.10+ and has no required dependencies (stdlib
only); this machine has 3.12.7. It does **not** need KiCad at runtime — it
parses saved `.kicad_sch` / `.kicad_pcb` files directly, and supports KiCad
5 through 10.

Optional, not set up: `DIGIKEY_CLIENT_ID` / `DIGIKEY_CLIENT_SECRET`,
`MOUSER_SEARCH_API_KEY`, `ELEMENT14_API_KEY`. Without them the sourcing skills
fall back to web search. LCSC needs no key, which is the one that matters if
the board goes to JLCPCB.

### What the review skills do and do not settle

The `kicad-happy` skills are a review pass, not an authority. Every §14.5
constraint is a geometric claim about the finished board — trace length,
copper at a node, cap-to-pin distance, return-path separation — and a passing
DRC says nothing about any of them. **Check them against the layout by
measuring, then have the skills review it.** Neither substitutes for the other.

---

## Routing policy

**The analog-critical nets below are routed by hand and are not handed to an
autorouter.** The reason is not aesthetic. This circuit's stability is set by a
parasitic — §3.1 puts stray capacitance at the op-amp inverting node at a pole
of **2–3 MHz, against a ~3 MHz crossover**, worth roughly **45° of phase
margin** — and an autorouter optimises for completion and length, with no model
of node capacitance, return-current paths, or differential symmetry. It will
produce a board that passes DRC and oscillates.

An autorouter is also the wrong tool for a one-revision board for a second
reason: its output is not reviewable. §14.5's constraints have to be *checked*,
and that requires routing someone chose.

### Hand-routed nets

Ordered by how much damage a bad route does.

| # | Net | Why it is hand-routed | Rule |
|---|---|---|---|
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
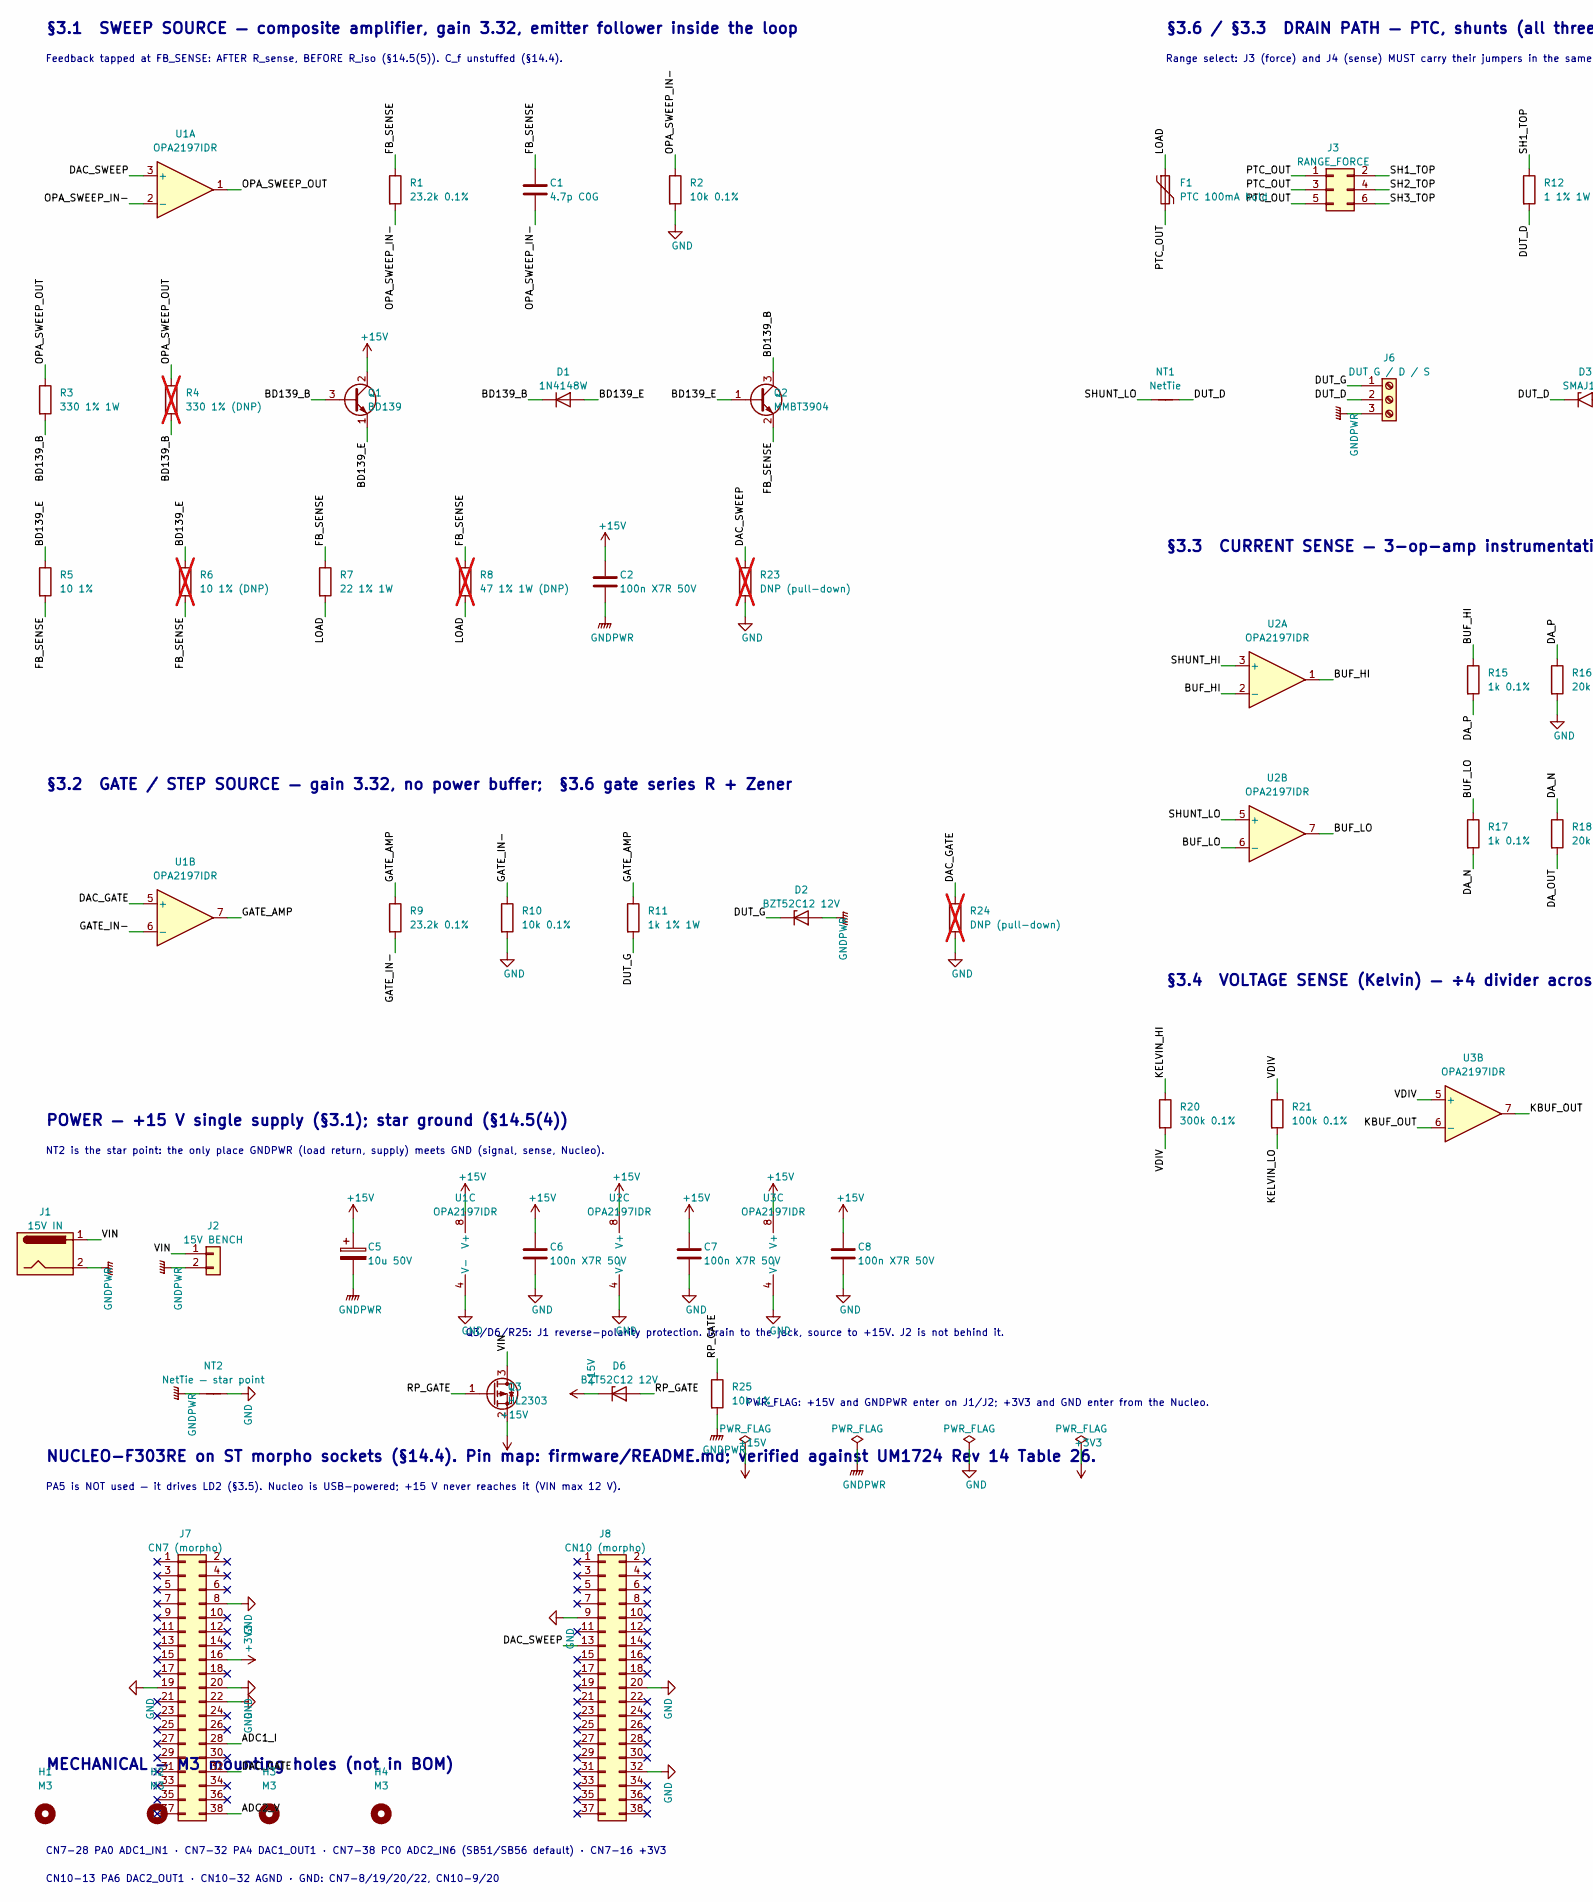
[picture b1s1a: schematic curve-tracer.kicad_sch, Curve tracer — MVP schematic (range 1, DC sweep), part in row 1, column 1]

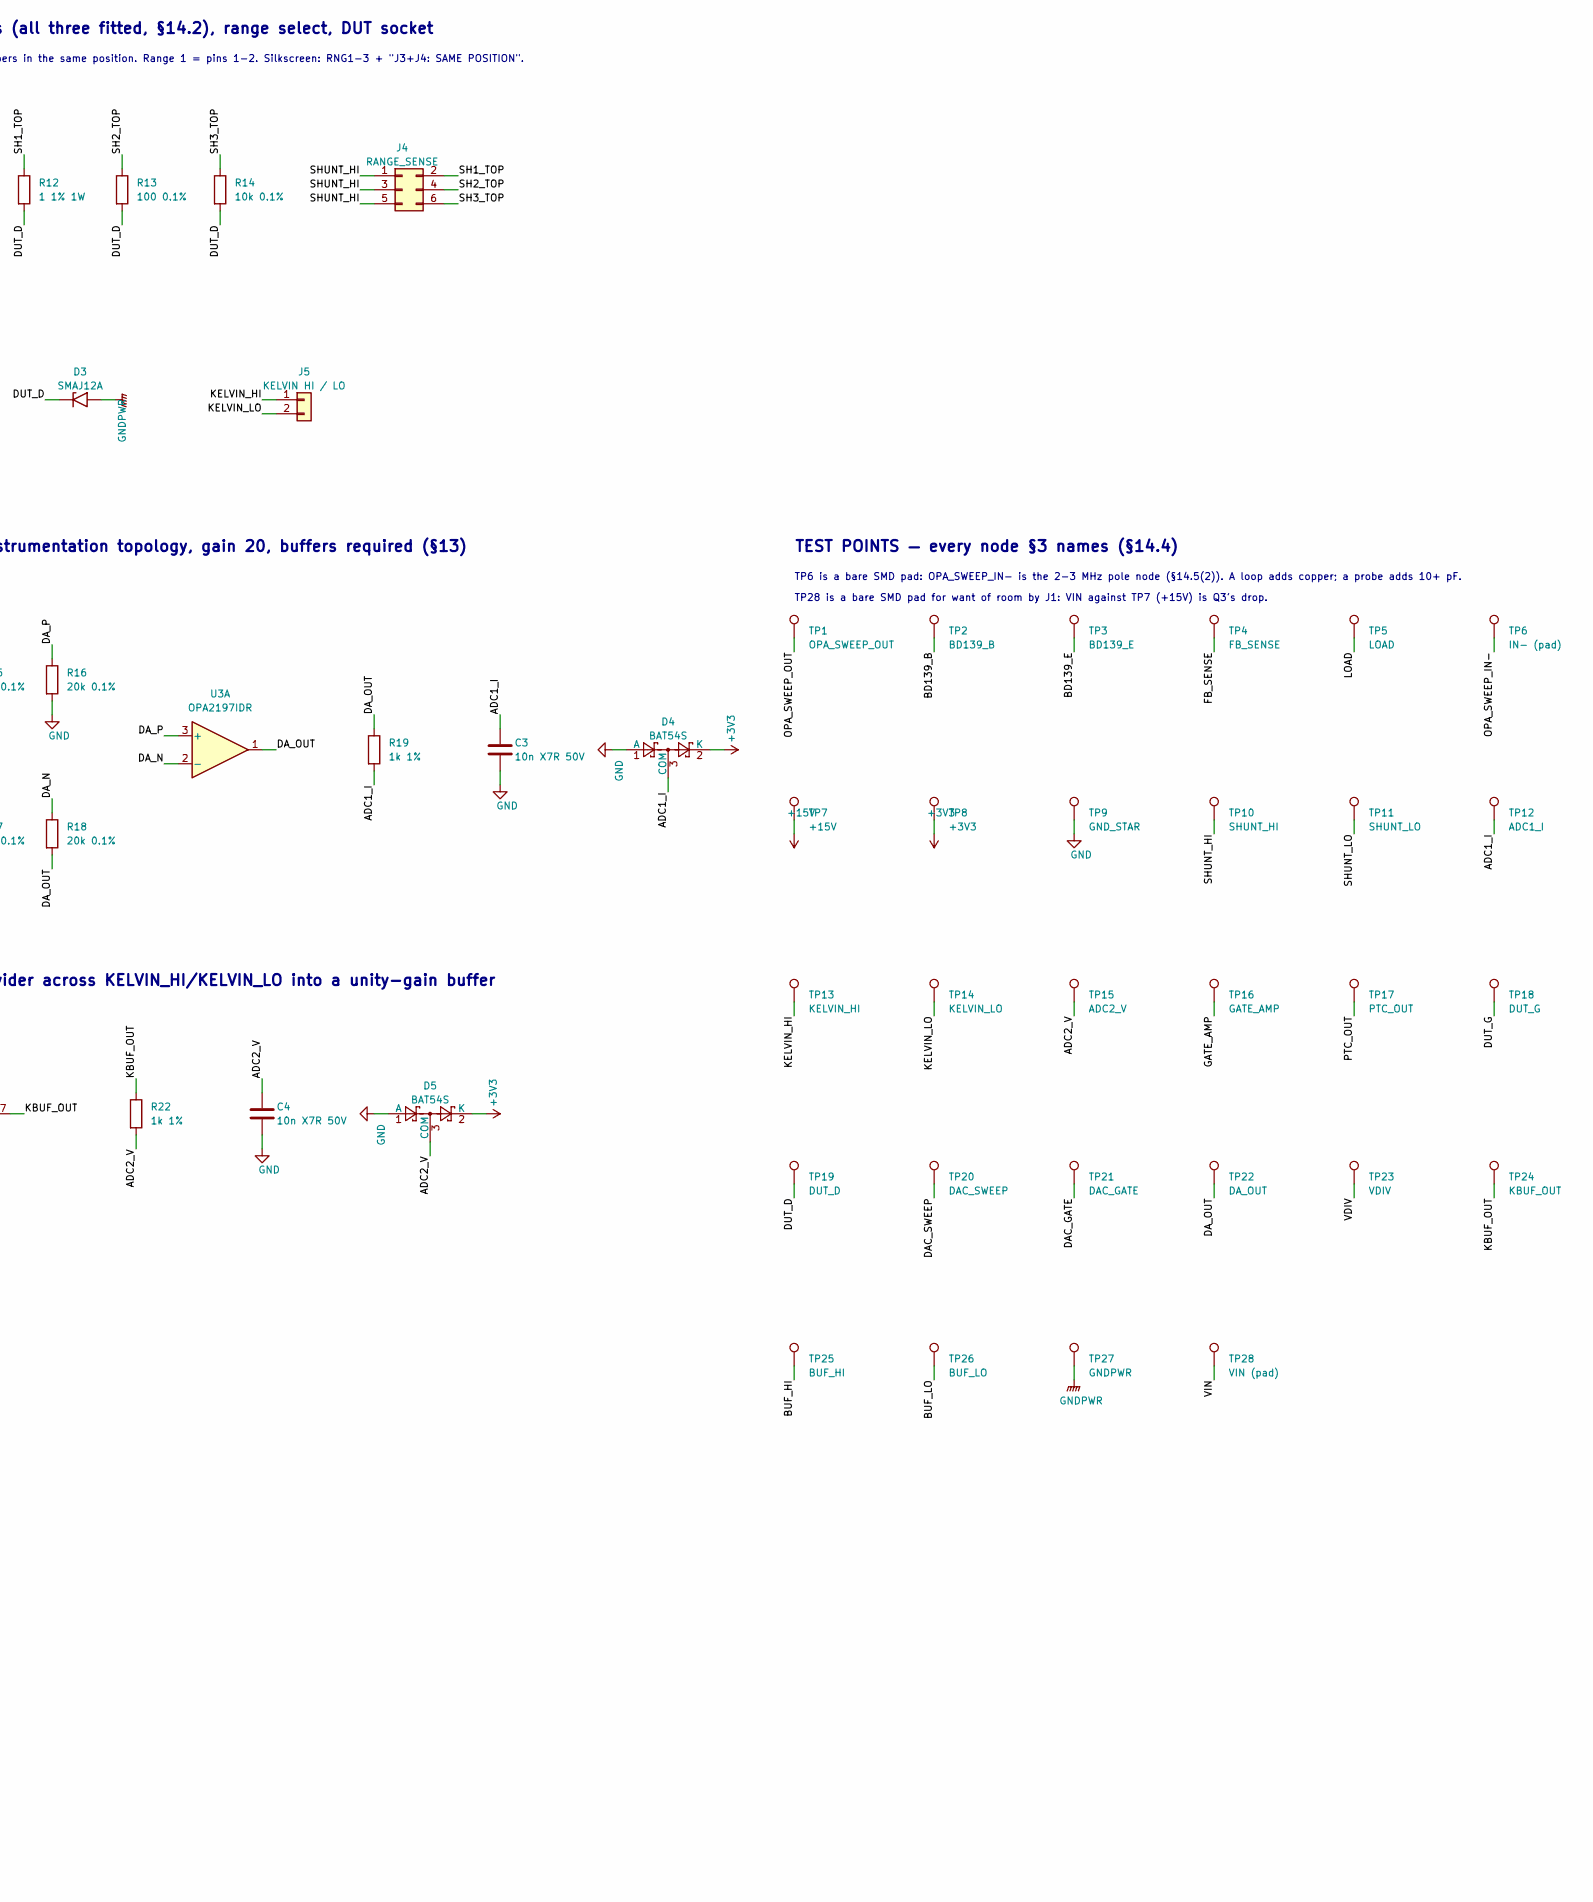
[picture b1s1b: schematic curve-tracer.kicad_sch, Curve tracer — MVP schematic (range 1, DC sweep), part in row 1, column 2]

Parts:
C1: 4.7p C0G; C_0603_1608Metric; MPN 0603CG4R7B500NT; LCSC C313086
C2, C6, C7, C8: 100n X7R 50V; C_0603_1608Metric; MPN CC0603KRX7R9BB104; LCSC C14663
C3, C4: 10n X7R 50V; C_0603_1608Metric; MPN 0603B103K500NT; LCSC C57112
C5: 10u 50V; CP_Elec_5x5.4; MPN RVT50V10M5X5; LCSC C47023118
D1: 1N4148W; D_SOD-123; MPN 1N4148W; LCSC C81598
D2, D6: BZT52C12 12V; D_SOD-123; MPN BZT52C12; LCSC C173429
D3: SMAJ12A; D_SMA; MPN SMAJ12A; LCSC C113957
D4, D5: BAT54S; SOT-23; MPN BAT54S; LCSC C7420333
F1: PTC 100mA hold; Fuse_1206_3216Metric; MPN nSMD010; LCSC C70065
H1, H2, H3, H4: M3; MountingHole_3.2mm_M3
J1: 15V IN; BarrelJack_Horizontal; MPN DC-005 2.0; LCSC C16214
J2: 15V BENCH; TerminalBlock_Phoenix_MKDS-1,5-2_1x02_P5.00mm_Horizontal; MPN KF301-5.0-2P; LCSC C474881
J3: RANGE_FORCE; PinHeader_2x03_P2.54mm_Vertical_RangeSelect; MPN PZ254V-12-6P; LCSC C492420
J4: RANGE_SENSE; PinHeader_2x03_P2.54mm_Vertical_RangeSelect; MPN PZ254V-12-6P; LCSC C492420
J5: KELVIN HI / LO; PinHeader_1x02_P2.54mm_Vertical; MPN PZ254V-11-02P; LCSC C492401
J6: DUT G / D / S; TerminalBlock_Phoenix_MKDS-1,5-3_1x03_P5.00mm_Horizontal; MPN KF301-5.0-3P; LCSC C474882
J7: CN7 (morpho); PinSocket_2x19_P2.54mm_Vertical_NucleoCarrier; MPN PM254-2-19-Z-8.5; LCSC C2897420
J8: CN10 (morpho); PinSocket_2x19_P2.54mm_Vertical_NucleoCarrier; MPN PM254-2-19-Z-8.5; LCSC C2897420
NT1: NetTie; NetTie-2_SMD_Pad0.5mm
NT2: NetTie — star point; NetTie-2_SMD_Pad0.5mm
Q1: BD139; TO-126-3_Vertical; MPN BD139; LCSC C27866
Q2: MMBT3904; SOT-23; MPN MMBT3904; LCSC C20526
Q3: HL2303; SOT-23; MPN HL2303; LCSC C7420345
R1, R9: 23.2k 0.1%; R_0603_1608Metric; MPN RT0603BRE0723K2L; LCSC C861768
R2, R10: 10k 0.1%; R_0603_1608Metric; MPN RT0603BRD0710KL; LCSC C95204
R3: 330 1% 1W; R_2512_6332Metric; MPN FRC2512F3300TS; LCSC C2934068
R4: 330 1% (DNP); R_Axial_DIN0309_L9.0mm_D3.2mm_P12.70mm_Horizontal; not fitted
R5: 10 1%; R_1206_3216Metric; MPN CRCW120610R0FKEAHP; LCSC C511457
R6: 10 1% (DNP); R_Axial_DIN0309_L9.0mm_D3.2mm_P12.70mm_Horizontal; not fitted
R7: 22 1% 1W; R_2512_6332Metric; MPN RC2512FK-0722RL; LCSC C276336
R8: 47 1% 1W (DNP); R_Axial_DIN0309_L9.0mm_D3.2mm_P12.70mm_Horizontal; MPN RN1WS47ΩFT/BA1; LCSC C385394; not fitted
R11: 1k 1% 1W; R_2512_6332Metric; MPN FRC2512F1001TS; LCSC C2960683
R12: 1 1% 1W; R_2512_6332Metric; MPN RC2512FK-071RL; LCSC C181756
R13: 100 0.1%; R_0805_2012Metric; MPN RT0805BRD07100RL; LCSC C110773
R14: 10k 0.1%; R_0805_2012Metric; MPN RT0805BRD0710KL; LCSC C110775
R15, R17: 1k 0.1%; R_0805_2012Metric; MPN RT0805BRD071KL; LCSC C110774
R16, R18: 20k 0.1%; R_0805_2012Metric; MPN RT0805BRD0720KL; LCSC C469660
R19, R22: 1k 1%; R_0603_1608Metric; MPN 0603WAF1001T5E; LCSC C21190
R20: 300k 0.1%; R_0603_1608Metric; MPN RT0603BRD07300KL; LCSC C705762
R21: 100k 0.1%; R_0603_1608Metric; MPN RT0603BRD07100KL; LCSC C122538
R23, R24: DNP (pull-down); R_0603_1608Metric; not fitted
R25: 10k 1%; R_0603_1608Metric; MPN 0603WAF1002T5E; LCSC C25804
TP1: OPA_SWEEP_OUT; TestPoint_Keystone_5000-5004_Miniature; MPN RH-5001; LCSC C5199801
TP2: BD139_B; TestPoint_Keystone_5000-5004_Miniature; MPN RH-5001; LCSC C5199801
TP3: BD139_E; TestPoint_Keystone_5000-5004_Miniature; MPN RH-5001; LCSC C5199801
TP4: FB_SENSE; TestPoint_Keystone_5000-5004_Miniature; MPN RH-5001; LCSC C5199801
TP5: LOAD; TestPoint_Keystone_5000-5004_Miniature; MPN RH-5001; LCSC C5199801
TP6: IN- (pad); TestPoint_Pad_D1.0mm
TP7: +15V; TestPoint_Keystone_5000-5004_Miniature; MPN RH-5001; LCSC C5199801
TP8: +3V3; TestPoint_Keystone_5000-5004_Miniature; MPN RH-5001; LCSC C5199801
TP9: GND_STAR; TestPoint_Keystone_5000-5004_Miniature; MPN RH-5001; LCSC C5199801
TP10: SHUNT_HI; TestPoint_Keystone_5000-5004_Miniature; MPN RH-5001; LCSC C5199801
TP11: SHUNT_LO; TestPoint_Keystone_5000-5004_Miniature; MPN RH-5001; LCSC C5199801
TP12: ADC1_I; TestPoint_Keystone_5000-5004_Miniature; MPN RH-5001; LCSC C5199801
TP13: KELVIN_HI; TestPoint_Keystone_5000-5004_Miniature; MPN RH-5001; LCSC C5199801
TP14: KELVIN_LO; TestPoint_Keystone_5000-5004_Miniature; MPN RH-5001; LCSC C5199801
TP15: ADC2_V; TestPoint_Keystone_5000-5004_Miniature; MPN RH-5001; LCSC C5199801
TP16: GATE_AMP; TestPoint_Keystone_5000-5004_Miniature; MPN RH-5001; LCSC C5199801
TP17: PTC_OUT; TestPoint_Keystone_5000-5004_Miniature; MPN RH-5001; LCSC C5199801
TP18: DUT_G; TestPoint_Keystone_5000-5004_Miniature; MPN RH-5001; LCSC C5199801
TP19: DUT_D; TestPoint_Keystone_5000-5004_Miniature; MPN RH-5001; LCSC C5199801
TP20: DAC_SWEEP; TestPoint_Keystone_5000-5004_Miniature; MPN RH-5001; LCSC C5199801
TP21: DAC_GATE; TestPoint_Keystone_5000-5004_Miniature; MPN RH-5001; LCSC C5199801
TP22: DA_OUT; TestPoint_Keystone_5000-5004_Miniature; MPN RH-5001; LCSC C5199801
TP23: VDIV; TestPoint_Keystone_5000-5004_Miniature; MPN RH-5001; LCSC C5199801
TP24: KBUF_OUT; TestPoint_Keystone_5000-5004_Miniature; MPN RH-5001; LCSC C5199801
TP25: BUF_HI; TestPoint_Keystone_5000-5004_Miniature; MPN RH-5001; LCSC C5199801
TP26: BUF_LO; TestPoint_Keystone_5000-5004_Miniature; MPN RH-5001; LCSC C5199801
TP27: GNDPWR; TestPoint_Keystone_5000-5004_Miniature; MPN RH-5001; LCSC C5199801
TP28: VIN (pad); TestPoint_Pad_D1.0mm
U1, U2, U3: OPA2197IDR; SOIC-8_3.9x4.9mm_P1.27mm; MPN OPA2197IDR; LCSC C139363

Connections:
+3V3: D4.2 (K), D5.2 (K), J7.16, TP8.1
+15V: C2.1, C5.1, C6.1, C7.1, C8.1, D6.1 (K), Q1.2 (C), Q3.2 (S), TP7.1, U1.8 (V+), U2.8 (V+), U3.8 (V+)
/ADC1_I: C3.1, D4.3 (COM), J7.28, R19.2, TP12.1
/ADC2_V: C4.1, D5.3 (COM), J7.38, R22.2, TP15.1
/BD139_B: D1.1 (K), Q1.3 (B), Q2.3 (C), R3.2, R4.2, TP2.1
/BD139_E: D1.2 (A), Q1.1 (E), Q2.1 (B), R5.1, R6.1, TP3.1
/BUF_HI: R15.1, TP25.1, U2.1, U2.2 (-)
/BUF_LO: R17.1, TP26.1, U2.6 (-), U2.7
/DAC_GATE: J7.32, R24.1, TP21.1, U1.5 (+)
/DAC_SWEEP: J8.13, R23.1, TP20.1, U1.3 (+)
/DA_N: R17.2, R18.1, U3.2 (-)
/DA_OUT: R18.2, R19.1, TP22.1, U3.1
/DA_P: R15.2, R16.1, U3.3 (+)
/DUT_D: D3.1 (A1), J6.2, NT1.2, R12.2, R13.2, R14.2, TP19.1
/DUT_G: D2.1 (K), J6.1, R11.2, TP18.1
/FB_SENSE: C1.1, Q2.2 (E), R1.1, R5.2, R6.2, R7.1, R8.1, TP4.1
/GATE_AMP: R9.1, R11.1, TP16.1, U1.7
/GATE_IN-: R9.2, R10.1, U1.6 (-)
/KBUF_OUT: R22.1, TP24.1, U3.6 (-), U3.7
/KELVIN_HI: J5.1, R20.1, TP13.1
/KELVIN_LO: J5.2, R21.2, TP14.1
/LOAD: F1.1, R7.2, R8.2, TP5.1
/OPA_SWEEP_IN-: C1.2, R1.2, R2.1, TP6.1, U1.2 (-)
/OPA_SWEEP_OUT: R3.1, R4.1, TP1.1, U1.1
/PTC_OUT: F1.2, J3.1, J3.3, J3.5, TP17.1
/RP_GATE: D6.2 (A), Q3.1 (G), R25.1
/SH1_TOP: J3.2, J4.2, R12.1
/SH2_TOP: J3.4, J4.4, R13.1
/SH3_TOP: J3.6, J4.6, R14.1
/SHUNT_HI: J4.1, J4.3, J4.5, TP10.1, U2.3 (+)
/SHUNT_LO: NT1.1, TP11.1, U2.5 (+)
/VDIV: R20.2, R21.1, TP23.1, U3.5 (+)
/VIN: J1.1, J2.1, Q3.3 (D), TP28.1
GND: C3.2, C4.2, C6.2, C7.2, C8.2, D4.1 (A), D5.1 (A), J7.8, J7.19, J7.20, J7.22, J8.9, J8.20, J8.32, NT2.2, R2.2, R10.2, R16.2, R23.2, R24.2, TP9.1, U1.4 (V-), U2.4 (V-), U3.4 (V-)
GNDPWR: C2.2, C5.2, D2.2 (A), D3.2 (A2), J1.2, J2.2, J6.3, NT2.1, R25.2, TP27.1

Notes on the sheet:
Feedback tapped at FB_SENSE: AFTER R_sense, BEFORE R_iso (§14.5(5)). C_f unstuffed (§14.4).
CN7-28 PA0 ADC1_IN1 · CN7-32 PA4 DAC1_OUT1 · CN7-38 PC0 ADC2_IN6 (SB51/SB56 default) · CN7-16 +3V3
PA5 is NOT used — it drives LD2 (§3.5). Nucleo is USB-powered; +15 V never reaches it (VIN max 12 V).
Range select: J3 (force) and J4 (sense) MUST carry their jumpers in the same position. Range 1 = pins 1-2. Silkscreen: RNG1-3 + "J3+J4: SAME POSITION".
§3.1 SWEEP SOURCE — composite amplifier, gain 3.32, emitter follower inside the loop
NUCLEO-F303RE on ST morpho sockets (§14.4). Pin map: firmware/README.md; verified against UM1724 Rev 14 Table 26.
MECHANICAL — M3 mounting holes (not in BOM)
TP28 is a bare SMD pad for want of room by J1: VIN against TP7 (+15V) is Q3's drop.
POWER — +15 V single supply (§3.1); star ground (§14.5(4))
§3.6 / §3.3 DRAIN PATH — PTC, shunts (all three fitted, §14.2), range select, DUT socket
CN10-13 PA6 DAC2_OUT1 · CN10-32 AGND · GND: CN7-8/19/20/22, CN10-9/20
TP6 is a bare SMD pad: OPA_SWEEP_IN- is the 2-3 MHz pole node (§14.5(2)). A loop adds copper; a probe adds 10+ pF.
TEST POINTS — every node §3 names (§14.4)
PWR_FLAG: +15V and GNDPWR enter on J1/J2; +3V3 and GND enter from the Nucleo.
§3.4 VOLTAGE SENSE (Kelvin) — ÷4 divider across KELVIN_HI/KELVIN_LO into a unity-gain buffer
Q3/D6/R25: J1 reverse-polarity protection. Drain to the jack, source to +15V. J2 is not behind it.
§3.2 GATE / STEP SOURCE — gain 3.32, no power buffer; §3.6 gate series R + Zener
NT2 is the star point: the only place GNDPWR (load return, supply) meets GND (signal, sense, Nucleo).
§3.3 CURRENT SENSE — 3-op-amp instrumentation topology, gain 20, buffers required (§13)
